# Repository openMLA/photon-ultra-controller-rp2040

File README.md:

> [!IMPORTANT]
> This repository has been archived as the implementation turned out to have too many limitations regarding memory. It will work for 2-bit images, but the newer approach is all around more capable. The replacement approach uses the DPI of a raspberry pi, and can be found at [openMLA/photon-ultra-controller](https://github.com/openMLA/photon-ultra-controller)

# Photon Ultra DLP controller

This repository contains PCB design files and code for a replacement mainboard for the [Anycubic Photon Ultra](https://www.anycubic.com/pages/anycubic-photon-ultra). 

The replacement board allows users to generate the signals required for the *DLP controller board* (designed by eViewTek) & DMD that comes with the photon ultra. It does not capture the full functionality of the Anycubic mainboard as it does not control the interface LCD, control the mechanics (stepper motor) or run any resin 3D printer slicer software. It **only** controls the DLP projector with an arbitrary 2-bit* 1240x720 image. Exposure time can be set per image.

This project might be of interest to you if you **own a photon ultra** and are interested in either

1. Using the photon ultra for PCB fabrication (use the DLP to expose a photoresist)
2. Are looking to use a DMD for other applications but are not ready to build your own controller board.

If you are interested in learning more about the Photon Ultra, you can find more information on [this photon ultra teardown blog post](https://nemoandrea.github.io/blog/Anycubic_DLP_teardown/). More images are available on request.

> If you have another board that uses the DMD chipset (e.g. Anycubic D2 or Mars 4 DLP), you can probably modify the project with minimal effort and get it to work for those boards too! (you would have to maybe have to adjust the traces to the FPC, and maybe tweak the physical connectors etc; but code and approach would be very similar)

### 💡 UV Patterns

> [!NOTE]  
> Due to RAM limitations (and my c programming skill limitations) the board can only display 2-bit images if you use the full resolution of the DMD. More RAM would solve this issue.

Below an example of the eViewTek board and optical engine controlled by the pico pio units, showing the OpenMLA project logo. Note that the pattern is 2-bit, so there are only 4 intensities (of which 1 is OFF).

Below another example of the 4 grayscale values that can be shown.

### PCB

The PCB uses a Raspberry Pi Pico board as the central controller. The PIO blocks of the RP2040 generate the timing signals for the DLPC1438 chip on the DLP controller board.

### Using the board

The board is shaped to fit in the original mainboard space. The buttons, usb-c programming port and barrel jack are all accessible through the original Photon Ultra enclosure. This means you can use the original fittings, and everything in terms of cables should just fit.

Of course if you do not plan on using the DMD in the context of the photon ultra, you could easily redesign the board to be much more compact.

### Code

The code for this project is written in C, and unfortunately I am not a C programmer so it is very sloppy code. If you know of ways to make parts more elegant don't hesitate to make a pull request with changes.

More important than the code is the approach taken to power up and control the photon board, and more specifically the DLPC1438. A walkthrough of steps and gotchas can be found in [the guidelines](Guidelines.md). Most of it will also be mentioned in the code for the project, but having a separate document is more convenient.

The PIO implementation is a modified version of the nice [writeup by Hunter Adams](https://vanhunteradams.com/Pico/VGA/VGA.html#Code-organization).

To convert images for display, there is a simple python utility that converts a grayscale image into the right byte format for display. You can run it on the demo images to verify assembly.

### Context

This work was developed as part of the [openMLA project](https://github.com/openMLA), where the goal is to build an open hardware lithography system. Eventually an open hardware DLP controller board will be published as part of openMLA, but this represents an intermediate step. 

### Project TODO

* ✅ Establish I2C communication with DLPC1438 

* ✅ Verify UCB programming and linear regulator

* ❓ Verify 12V power delivery to board (should be fine as of version 0.1.4)

* ✅ Verify 51-pin connector and pinout is correct

* ✅ Verify (2-bit) images can be sent and projected

* ❓ Implement SPI interface for transferring images to the pico

* ❓ Minimise flickering

## Acknowledgements

The following KiCAD external libraries were used

* [Raspberry pi pico by ncarandini](https://github.com/ncarandini/KiCad-RP-Pico)

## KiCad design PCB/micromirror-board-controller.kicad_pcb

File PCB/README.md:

### PCB design

The design uses a Raspberry pi Pico W. A non-wireless version can also work but some of the scripts are to be built around wireless connectivity for data transfer. See the schematic (below and [as a pdf](schematic.pdf)) for more info.

### Assembly

Most components are SMD, and the mouser links can be found in the basic [BOM](BOM.csv). In addition to the components of the BOM, you will also need some small wires to connect the USB data lines.

A solderpaste stencil might be worthwhile, as that FPC connector is pretty challenging (but not impossible) to handsolder.

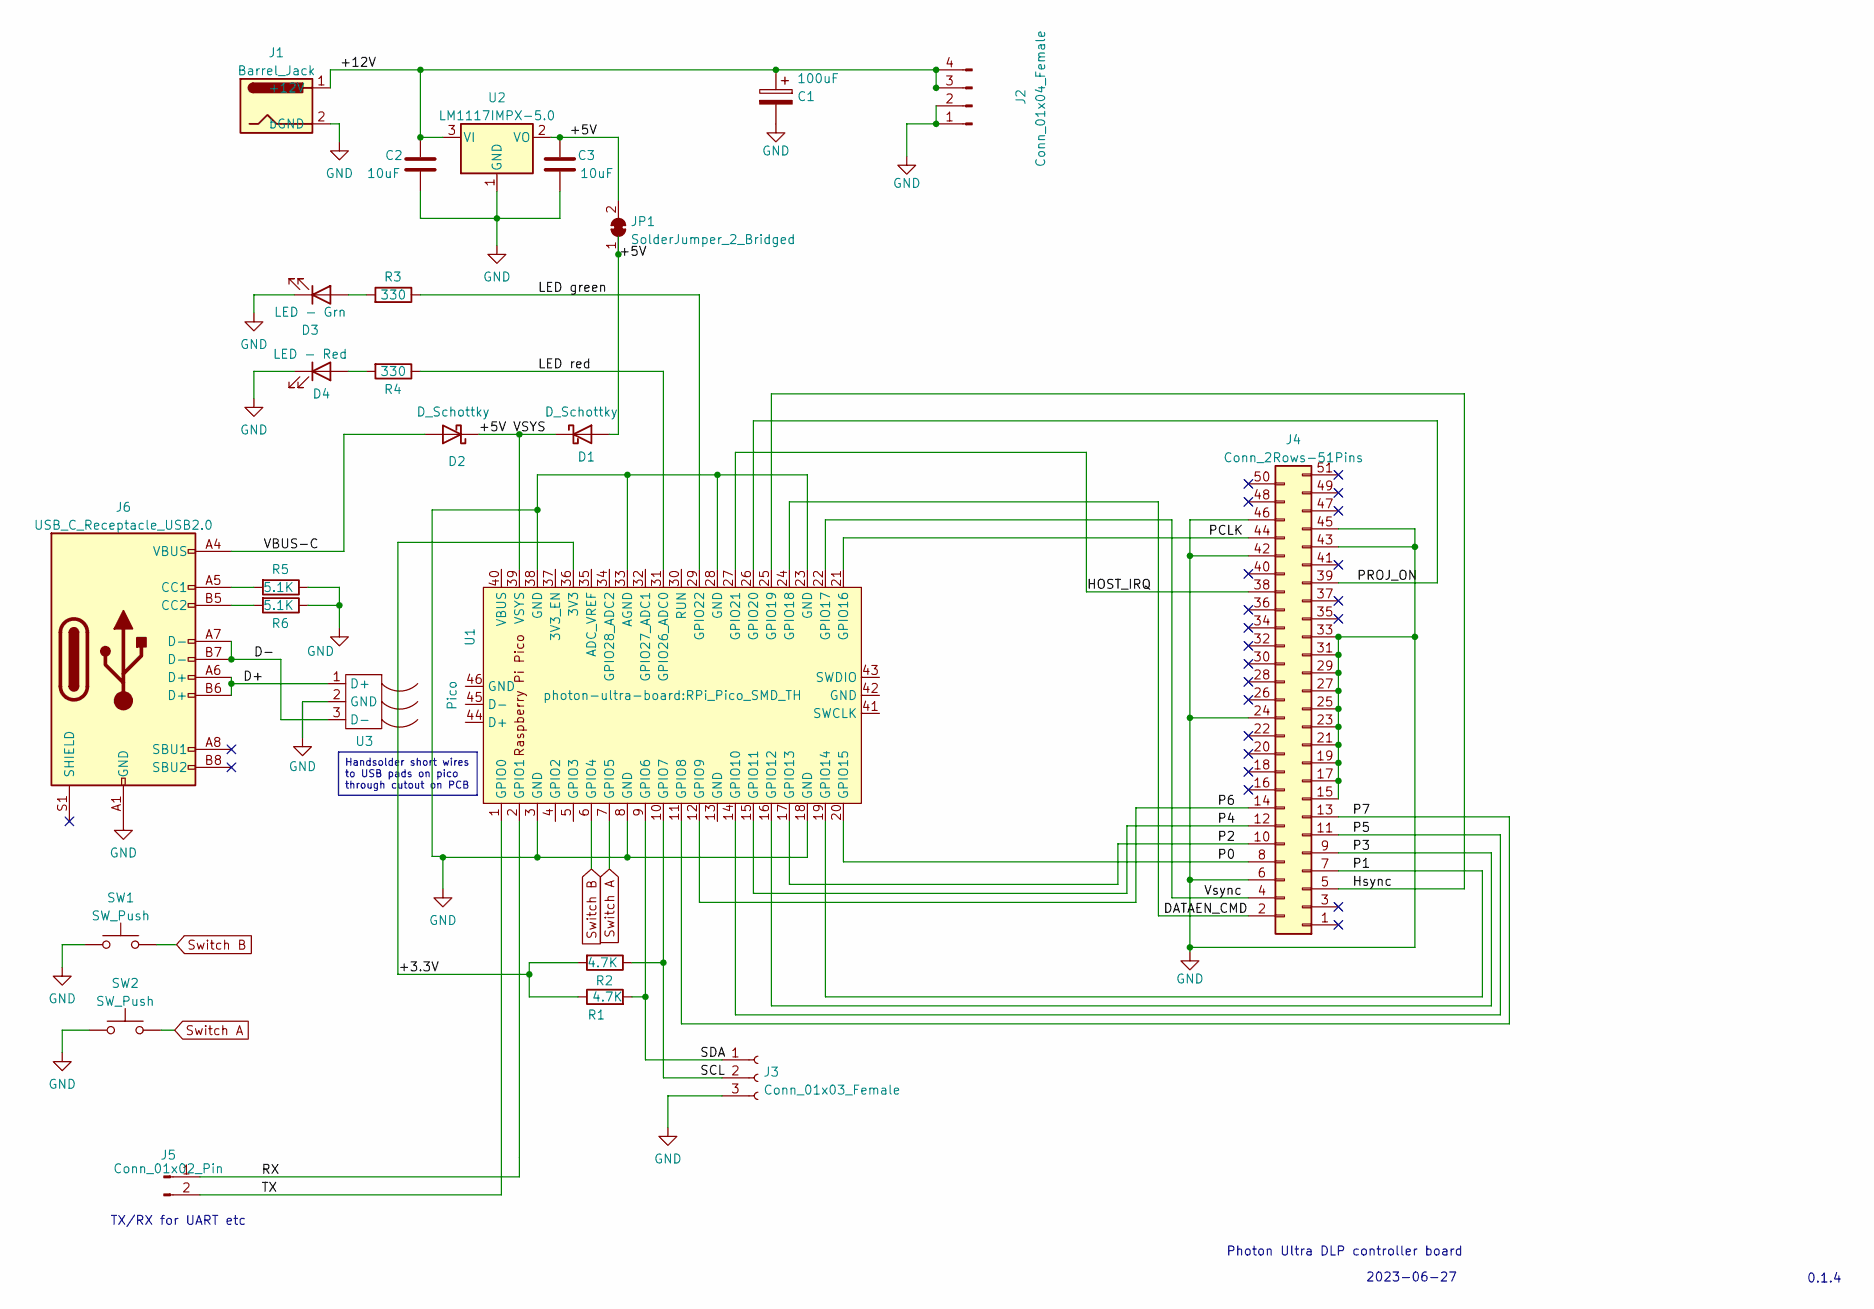
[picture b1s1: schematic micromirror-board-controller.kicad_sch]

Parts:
C1: 100uF; CP_Elec_6.3x7.7
C2, C3: 10uF; C_0805_2012Metric_Pad1.18x1.45mm_HandSolder
D1, D2: D_Schottky; D_SOD-323_HandSoldering
D3: LED - Grn; LED_0805_2012Metric
D4: LED - Red; LED_0805_2012Metric
J1: Barrel_Jack; BarrelJack_GCT_DCJ200-10-A_Horizontal
J2: Conn_01x04_Female; JST_PH_B4B-PH-SM4-TB_1x04-1MP_P2.00mm_Vertical
J3: Conn_01x03_Female; JST_PH_B3B-PH-SM4-TB_1x03-1MP_P2.00mm_Vertical
J4: Conn_2Rows-51Pins; Molex_502250-5191_2Rows-51Pins-1MP_P0.60mm_Horizontal
J5: Conn_01x02_Pin; PinHeader_1x02_P2.54mm_Horizontal
J6: USB_C_Receptacle_USB2.0; USB_C_Receptacle_HRO_TYPE-C-31-M-12
JP1: SolderJumper_2_Bridged; SolderJumper-2_P1.3mm_Bridged_RoundedPad1.0x1.5mm
R1, R2: 4.7K; R_1206_3216Metric
R3, R4: 330; R_1206_3216Metric
R5, R6: 5.1K; R_1206_3216Metric
SW1, SW2: SW_Push; SW_Tactile_SPST_Angled_PTS645Vx83-2LFS
U1: Pico; RPi_Pico_SMD_TH
U2: LM1117IMPX-5.0; TO-252-3_TabPin2
U3: usb-handsolder-pads

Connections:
/+3.3V: R1.1, R2.2, U1.36 (3V3)
/+5V: C3.1, D1.2 (A), JP1.1 (A), JP1.2 (B), U2.2 (VO); also elsewhere on the board
/+5V VSYS: D1.1 (K), D2.1 (K), U1.39 (VSYS)
/+12V: C1.1, C2.1, J1.1 (+12V), J2.3, J2.4, U2.3 (VI)
/D+: J6.A6 (D+), J6.B6 (D+), U3.1 (D+)
/D-: J6.A7 (D-), J6.B7 (D-), U3.3 (D-)
/DATAEN_CMD: J4.2 (DATAEN), U1.24 (GPIO18)
/HOST_IRQ: J4.38 (HOST_IRQ), U1.27 (GPIO21)
/Hsync: J4.5 (Hsync), U1.25 (GPIO19)
/LED green: R3.1, U1.29 (GPIO22)
/LED red: R4.1, U1.31 (GPIO26_ADC0)
/P0: J4.8 (P0), U1.20 (GPIO15)
/P1: J4.7 (P1), U1.19 (GPIO14)
/P2: J4.10 (P2), U1.17 (GPIO13)
/P3: J4.9 (P3), U1.16 (GPIO12)
/P4: J4.12 (P4), U1.15 (GPIO11)
/P5: J4.11 (P5), U1.14 (GPIO10)
/P6: J4.14 (P6), U1.12 (GPIO9)
/P7: J4.13 (P7), U1.11 (GPIO8)
/PCLK: J4.44 (PCLK), U1.21 (GPIO16)
/PROJ_ON: J4.39 (GPIO_9), U1.26 (GPIO20)
/RX: J5.1, U1.2 (GPIO1)
/SCL: J3.2 (SCL), R2.1, U1.10 (GPIO7)
/SDA: J3.1 (dGND), R1.2, U1.9 (GPIO6)
/TX: J5.2, U1.1 (GPIO0)
/VBUS-C: D2.2 (A), J6.A4 (VBUS), J6.A9 (VBUS), J6.B4 (VBUS), J6.B9 (VBUS)
/Vsync: J4.4 (Vsync), U1.22 (GPIO17)
GND: C1.2, C2.2, C3.2, D3.1 (K), D4.1 (K), J1.2 (bGND), J2.1, J2.2, J3.3 (SDA), J4.6 (GND), J4.15 (GND), J4.17, J4.19, J4.21, J4.23, J4.24, J4.25, J4.27, J4.29, J4.31, J4.33, J4.42 (GND), J4.43 (GND), J4.45 (GND), J4.46 (GND), J6.A1 (GND), J6.A12 (GND), J6.B1 (GND), J6.B12 (GND), R5.1, R6.1, SW1.1, SW2.1, U1.3 (GND), U1.8 (GND), U1.18 (GND), U1.23 (GND), U1.28 (GND), U1.33 (AGND), U1.38 (GND), U2.1 (GND), U3.2 (GND); also elsewhere on the board
unnamed: D3.2 (A), R3.2
unnamed: D4.2 (A), R4.2
unnamed: J6.A5 (CC1), R5.2
unnamed: J6.B5 (CC2), R6.2
Switch A: SW2.2, U1.7 (GPIO5)
Switch B: SW1.2, U1.6 (GPIO4)

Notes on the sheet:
Handsolder short wires to USB pads on pico through cutout on PCB
TX/RX for UART etc
Photon Ultra DLP controller board
2023-06-27
0.1.4

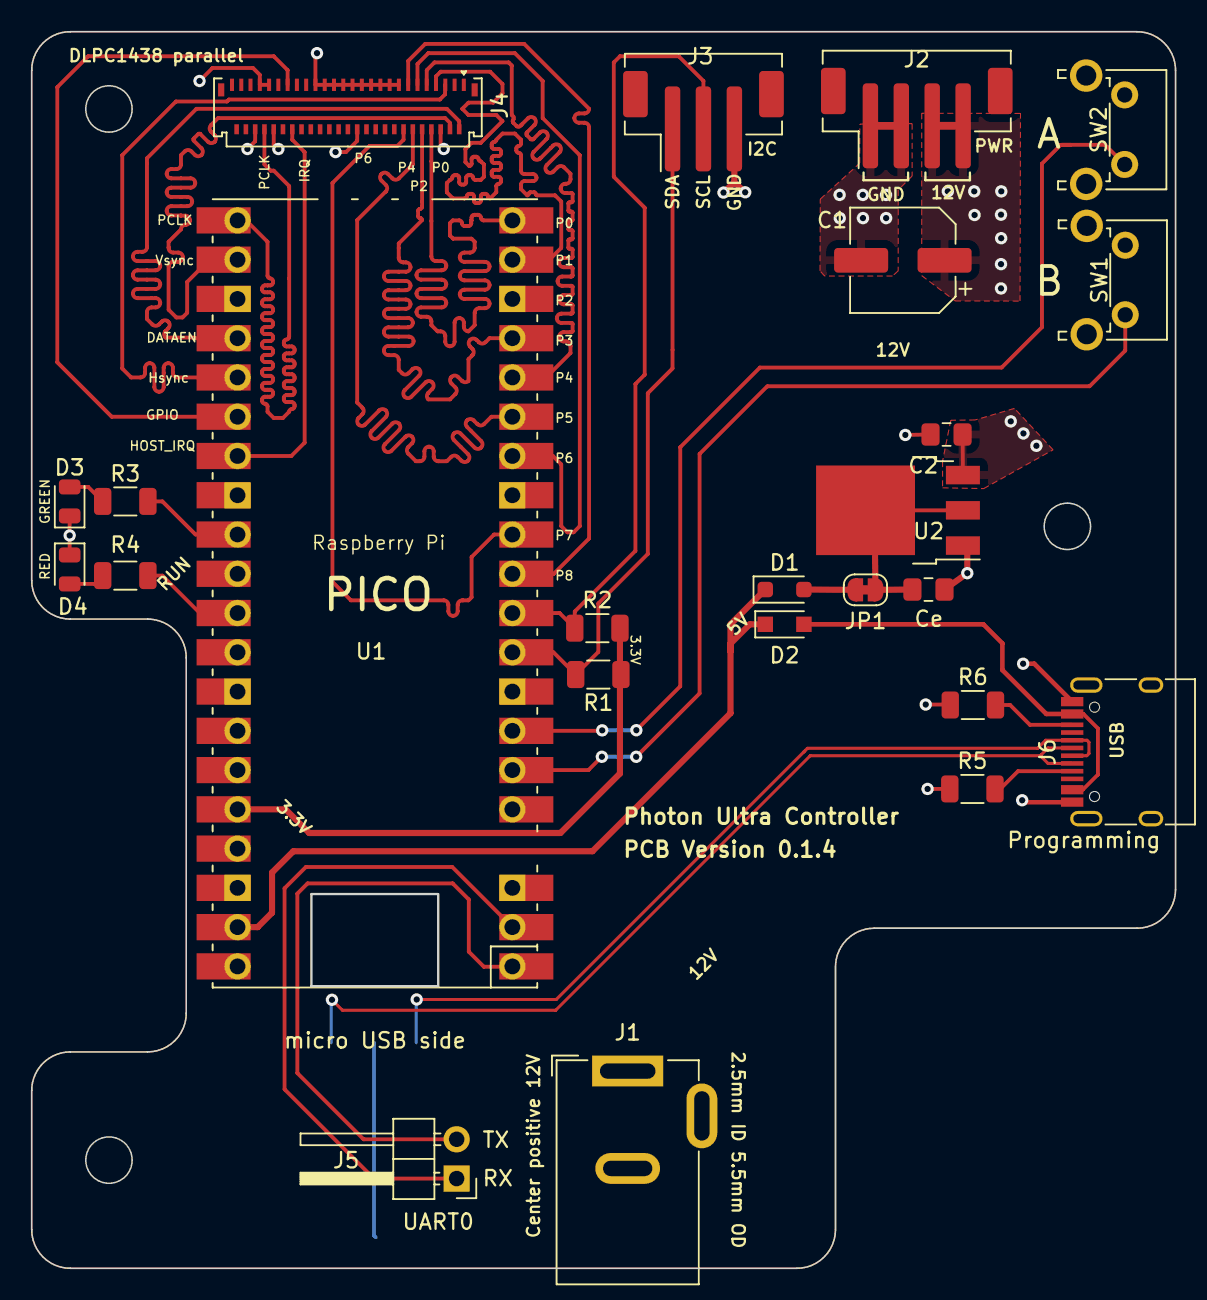
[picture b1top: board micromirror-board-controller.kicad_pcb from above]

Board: 2 copper layers, 74.0 x 80.0 mm, 25 parts (1 on the bottom side), 34 nets.

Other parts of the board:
Ce: 10uF; C_0805_2012Metric_Pad1.18x1.45mm_HandSolder

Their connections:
/+5V: Ce.1; also elsewhere on the board
GND: Ce.2; also elsewhere on the board

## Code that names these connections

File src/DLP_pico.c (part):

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 * Uses PIO-assembly of RP2040
 *
 * HARDWARE CONNECTIONS
 *  - GPIO 19 ---> Hsync
 *  - GPIO 18 ---> DATAEN_CMD (data valid) 
 *  - GPIO 17 ---> Vsync
 *  - GPIO 16 ---> PCLK (pixel clock)
 *  - GPIO 8:15 ---> Pdata[0:8] (pixel data 8bit grayscale)
 *
 * RESOURCES USED
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#include "pxl.pio.h"
#include "pxl_clk.pio.h"

const int PROJ_ON_GPIO = 20;  // physical pin nr 26
const int HOST_IRQ_GPIO = 21;  // physical pin nr 27  

const uint LED_PIN_G = 26;  // GPIO 26
const uint LED_PIN_R = 22;  // GPIO 26
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const int DLPC_addr = 0x1B;  

void initialise_DLPC() {  
    gpio_init(PROJ_ON_GPIO);
    gpio_set_dir(PROJ_ON_GPIO, GPIO_OUT);
    gpio_init(HOST_IRQ_GPIO);
    gpio_set_dir(HOST_IRQ_GPIO, GPIO_IN);
    bool current_IRQ_state = 0;

    printf(">> Attempting to initialise the DLPC1438...\n\n");

    // HOST_IRQ will be pulled HIGH by the pullup on eViewTek board
    // but in theory it could also be LOW at this time
    current_IRQ_state = gpio_get(HOST_IRQ_GPIO);  
    printf("HOST_IRQ at startup is: %d\n", current_IRQ_state);
    

    // to signal to the DLPC1438 that we want to start up, we must set PROJ_ON high
    printf("Setting PROJ_ON (DLPC1436:GPIO8) HIGH...\n");
    gpio_put(PROJ_ON_GPIO, 1);  // this will let the DLPC1438 know we want to go, go go

    // now we must let the DLPC1438 run through its initialisation cycle
    // it will let us know it is done by pulling HOST_IRQ low (~500ms)
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
    // while (!transition) {
    //     sleep_ms(sleeptime);
    //     current_IRQ_state = gpio_get(HOST_IRQ_GPIO);  
    //     //printf("HOST IRQ IS: %d\n", current_IRQ_state);
    //     if ((last_IRQ_state == 1) && (current_IRQ_state == 0)) { transition = 1; }
    //     last_IRQ_state = current_IRQ_state;
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
// Give the I/O pins that we're using some names that make sense
// the pins match the layout in the PCB and the pico board pinout
#define DATAEN_CMD   18
#define HSYNC     19
#define VSYNC     17
#define PXL_CLK   16
#define BASE_PXL_PIN   8  // first pin (of 8) contiguous pixel bits

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    // is consolidated in one place. Here in the C, we then just import and use it.
    hsync_program_init(pio, hsync_sm, hsync_offset, HSYNC);
    vsync_program_init(pio, vsync_sm, vsync_offset, VSYNC);
    pxl_program_init(pio, pxl_sm, pxl_offset, BASE_PXL_PIN, DATAEN_CMD);
    pxl_clk_program_init(pio, clk_sm, clk_offset, PXL_CLK);


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
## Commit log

2023-03-25 Clean up board silkscreen
    Cleaned up silkscreen and added schematic pdf
2023-03-26 Rough draft for PIO programs
2023-03-26 Rearrangement of PCB traces and length matching
    Needed to rearrange pins. Matched trace lengths; probably overkill.
2023-03-26 Finalised length-matched PCB
    Fixed final few remaining traces with the new board layout.
2023-03-27 Clean up code directory
    Do some much-needed housekeeping for the rp2040 code.
2023-03-28 Set up pins and state machines
    Set up the correct pinout, configure the 4 state machines. Basic (approximate) timings are in place but demo pixel data still needs to be generated.
2023-03-31 4pixels per byte and demo code
    Due to memory constraints I moved to 2 bits per pixel instead of 8. Added simple checkerboard grayscale demo code. Timings still need timing optimisation and verification.
2023-03-31 Move to USB-C connector
    Replacing the original type-A connector now a type-C connector. CC1/2 terminated with 5.1k.
2023-03-31 Add openMLA logo
    Added logo and fixed missing ground connection on FPC. Did some cleanup with DRC.
2023-03-31 Add PCB preview image
2023-04-01 Add licence
    Add software and hardware licence. Added open hardware and licence info to PCB.
2023-05-23 Update readme
    Clarified state of project in main readme.
2023-05-23 Update README.md
    Fix warning admonition not being rendered correctly
2023-06-03 Fix licence error
2023-06-03 Complete schematic parts list
    Fix some parts without purchase link and clean up directory a bit.
2023-06-27 Improved USB lines connectivity
    Fixed the tricky blind SMD pad approach with cutout and backside wire connection. Added some 3D models for all board components. Reworked some silkscreen. Added a TX/RX serial connector for convenien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
2023-07-15 Fix +12V pinout and revise board
    Fixed the 12V board pinout (apparently GND and VSUP are swapped). Some early code on talking to the DLPC1438; not all verified to be correct yet.
2023-07-15 Fix markdown link
2023-10-24 First move to new serial code
    Add basic I2C check code
2023-10-24 Basic testpattern controls
    Added some work in progress commands to switch to test mode and back and check illumination status,
2023-10-25 Add skeleton for SPI image projection
    Add the required I2C commands for SPI pattern projection. Still lacking SPI data transfer function.
2023-10-26 Initial SPI approach
    Uses TI sample code which is not included in repository in the current form due to concerns about copyright.
2024-01-05 Update source files
2024-01-05 Functional startup code
    Tested startup cycle code in initialise_DLPC(). Confirmed to work with the parallel FPC interface on the development board.
2024-01-06 standby mode and early external print checks
2024-01-18 More functional I2C communication
2024-01-20 Clean up compiler warnings and unify modeswitch into single function
2024-01-20 Add updated uf2 file
2024-01-20 Fix shadowed variable/mixup
2024-01-20 Clean up syntax and some warnings
2024-01-20 Clean up testpattern code
    After some testing I think the i2c responses for testpattern are valid, although the pattern is still not projected as expected. But at least I2C seems good now.
2024-01-20 add flood exposure function and clean up some code
2024-01-21 Add more README information on development
2024-01-21 Select correct LED and integrate more I2C settings
    Integrate findings from I2C commands sent and their values from the original anycubic board.
2024-01-22 Patch for HOST_IRQ detection
    Dirty fix for the HOST_IRQ detection which is unreliable due to different voltage levels of DLPC1438. Added some debugging changes which will be reverted later I suspect.
2024-01-23 Correct Basic code for External Print Mode
    To be perfectly honest, I am not sure why it is working now, but it was not working before. Maybe something was changed on the hardware side, but this correctly displays some kind of data from the pa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
2024-01-24 add utility function to convert image to projector byte format
2024-01-25 Working 1-bit image
2024-01-25 Add test image template file
    leaving it empty to keep the repository size small
2024-01-25 Working 2bit image display
    Tested 2-bit image display (4 grayscale values). Patterns look okay, but image seems to be flickering a bit; need to check if that can be improved
2024-01-25 Update image converter for 2-bit format
    Updated the python utilitty to convert grayscale tifs into the 2-bit format that can be used in the pico code.
2024-01-25 Update readme with 2-bit images
    Update the readme to reflect the milestone of functional 2-bit images.
2024-01-25 Fix readme issue
2024-04-12 Add archiving message
    The repository will be renamed and archived. The replacement efforts will use the raspberry pi DPI capabilities instead.

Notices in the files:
PCB/micromirror-board-controller.kicad_pcb:
CERN-OHL-W-2.0
Licenced under
B.SilkS
